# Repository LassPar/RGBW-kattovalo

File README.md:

# RGBW-kattovalo
Puhelimella ohjattava RGBW kattovalo

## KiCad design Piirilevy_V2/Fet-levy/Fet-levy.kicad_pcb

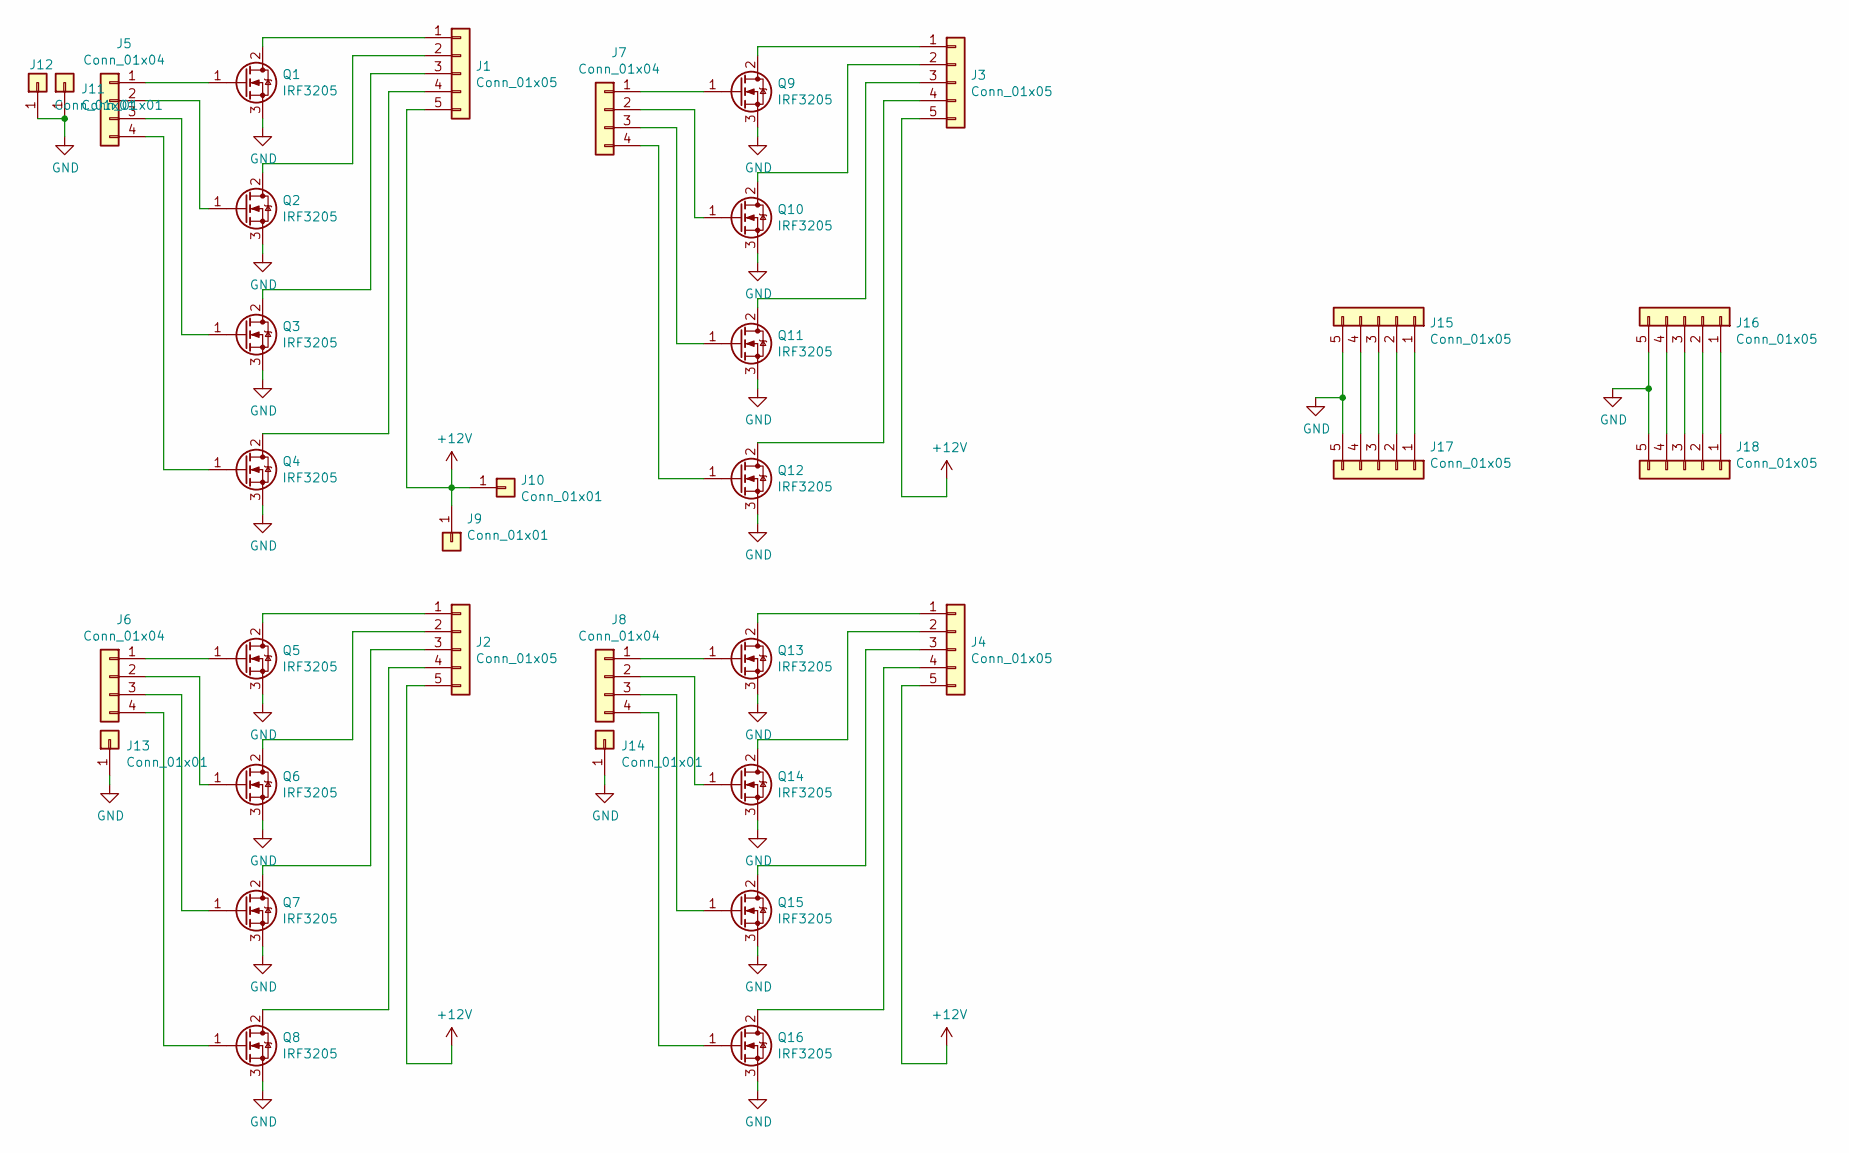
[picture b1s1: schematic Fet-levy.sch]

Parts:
J1, J2, J3, J4: Conn_01x05; JST_VH_B5P-VH-B_1x05_P3.96mm_Vertical
J5, J6, J7, J8: Conn_01x04; PinHeader_1x04_P2.54mm_Vertical
J9, J10, J11, J12, J13, J14: Conn_01x01; PinHeader_1x01_P2.54mm_Vertical
J15, J16, J17: Conn_01x05; PinHeader_1x05_P2.54mm_Vertical
J18: Conn_01x05; JST_XH_B05B-XH-A_1x05_P2.50mm_Vertical
Q1, Q2, Q3, Q4, Q5, Q6, Q7, Q8, Q9, Q10, Q11, Q12, Q13, Q14, Q15, Q16: IRF3205; TO-220-3_Vertical

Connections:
+12V: J1.5, J2.5, J3.5, J4.5, J9.1, J10.1
GND: J11.1, J12.1, J13.1, J14.1, J15.5, J16.5, J17.5, J18.5, Q1.3 (S), Q2.3 (S), Q3.3 (S), Q4.3 (S), Q5.3 (S), Q6.3 (S), Q7.3 (S), Q8.3 (S), Q9.3 (S), Q10.3 (S), Q11.3 (S), Q12.3 (S), Q13.3 (S), Q14.3 (S), Q15.3 (S), Q16.3 (S)
unnamed: J1.1, Q1.2 (D)
unnamed: J1.2, Q2.2 (D)
unnamed: J1.3, Q3.2 (D)
unnamed: J1.4, Q4.2 (D)
unnamed: J2.1, Q5.2 (D)
unnamed: J2.2, Q6.2 (D)
unnamed: J2.3, Q7.2 (D)
unnamed: J2.4, Q8.2 (D)
unnamed: J3.1, Q9.2 (D)
unnamed: J3.2, Q10.2 (D)
unnamed: J3.3, Q11.2 (D)
unnamed: J3.4, Q12.2 (D)
unnamed: J4.1, Q13.2 (D)
unnamed: J4.2, Q14.2 (D)
unnamed: J4.3, Q15.2 (D)
unnamed: J4.4, Q16.2 (D)
unnamed: J5.1, Q1.1 (G)
unnamed: J5.2, Q2.1 (G)
unnamed: J5.3, Q3.1 (G)
unnamed: J5.4, Q4.1 (G)
unnamed: J6.1, Q5.1 (G)
unnamed: J6.2, Q6.1 (G)
unnamed: J6.3, Q7.1 (G)
unnamed: J6.4, Q8.1 (G)
unnamed: J7.1, Q9.1 (G)
unnamed: J7.2, Q10.1 (G)
unnamed: J7.3, Q11.1 (G)
unnamed: J7.4, Q12.1 (G)
unnamed: J8.1, Q13.1 (G)
unnamed: J8.2, Q14.1 (G)
unnamed: J8.3, Q15.1 (G)
unnamed: J8.4, Q16.1 (G)
unnamed: J15.1, J17.1
unnamed: J15.2, J17.2
unnamed: J15.3, J17.3
unnamed: J15.4, J17.4
unnamed: J16.1, J18.1
unnamed: J16.2, J18.2
unnamed: J16.3, J18.3
unnamed: J16.4, J18.4

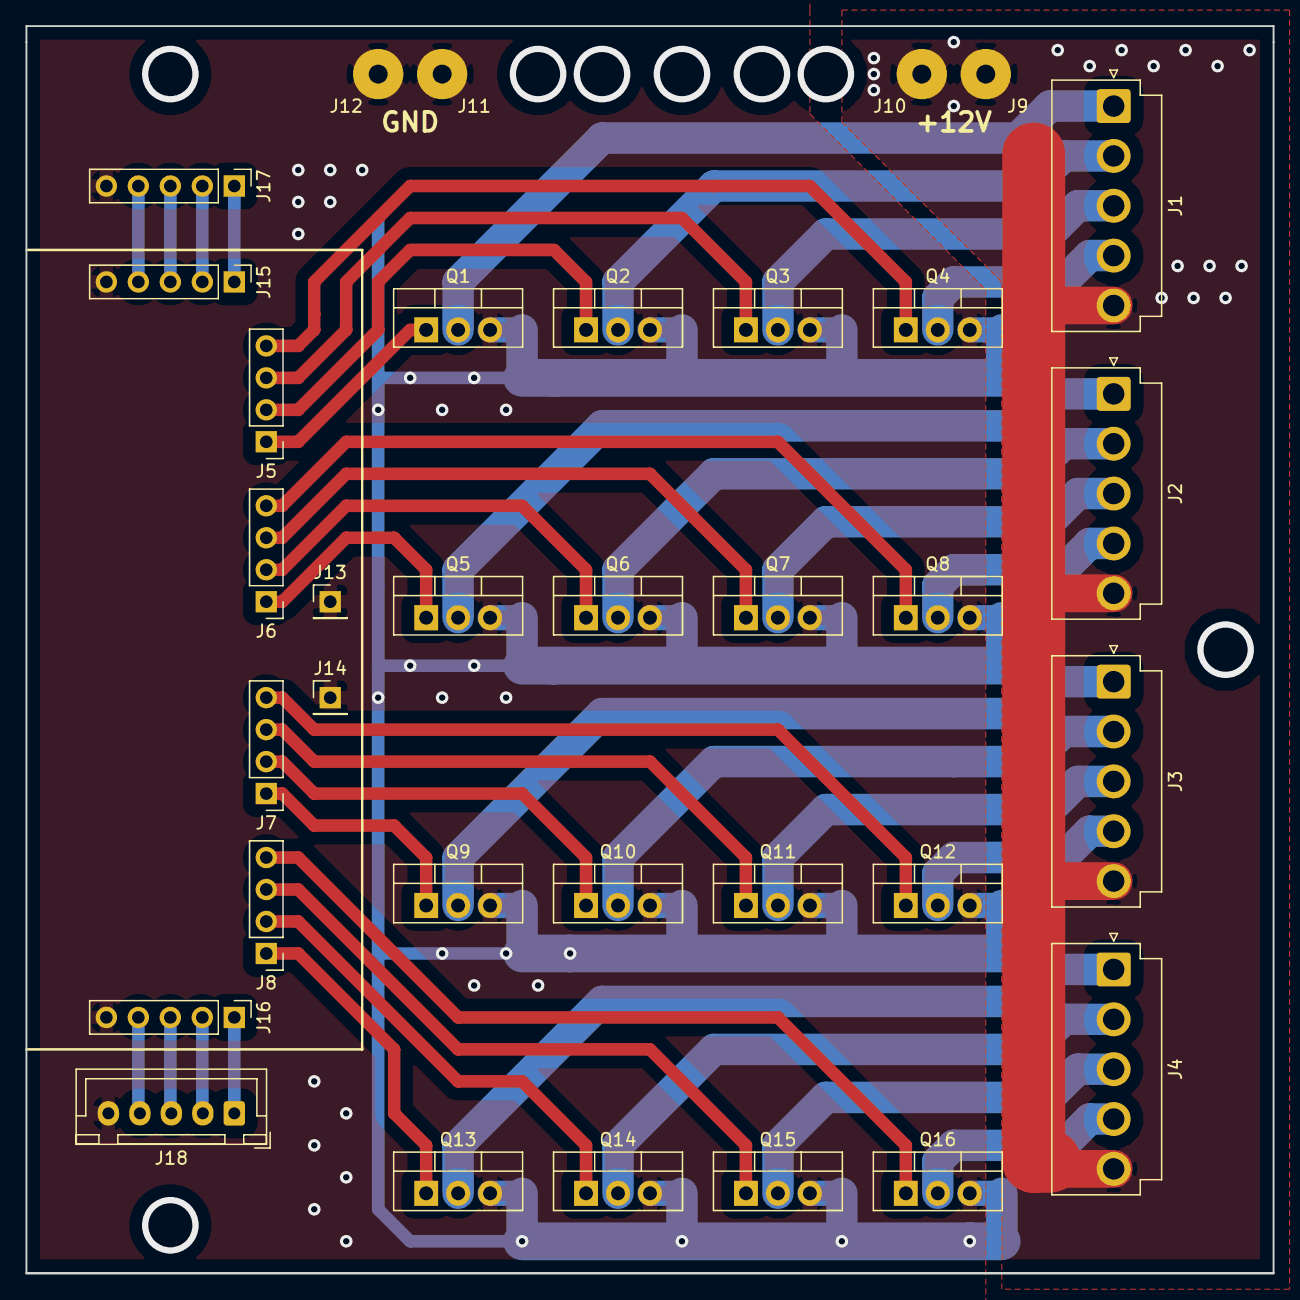
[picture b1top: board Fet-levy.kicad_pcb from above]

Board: 2 copper layers, 99.1 x 99.1 mm, 34 parts (0 on the bottom side), 42 nets.

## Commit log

2019-02-07 Piirilevy
2019-02-07 Koodia, ei testattu eikä läpiluettu
